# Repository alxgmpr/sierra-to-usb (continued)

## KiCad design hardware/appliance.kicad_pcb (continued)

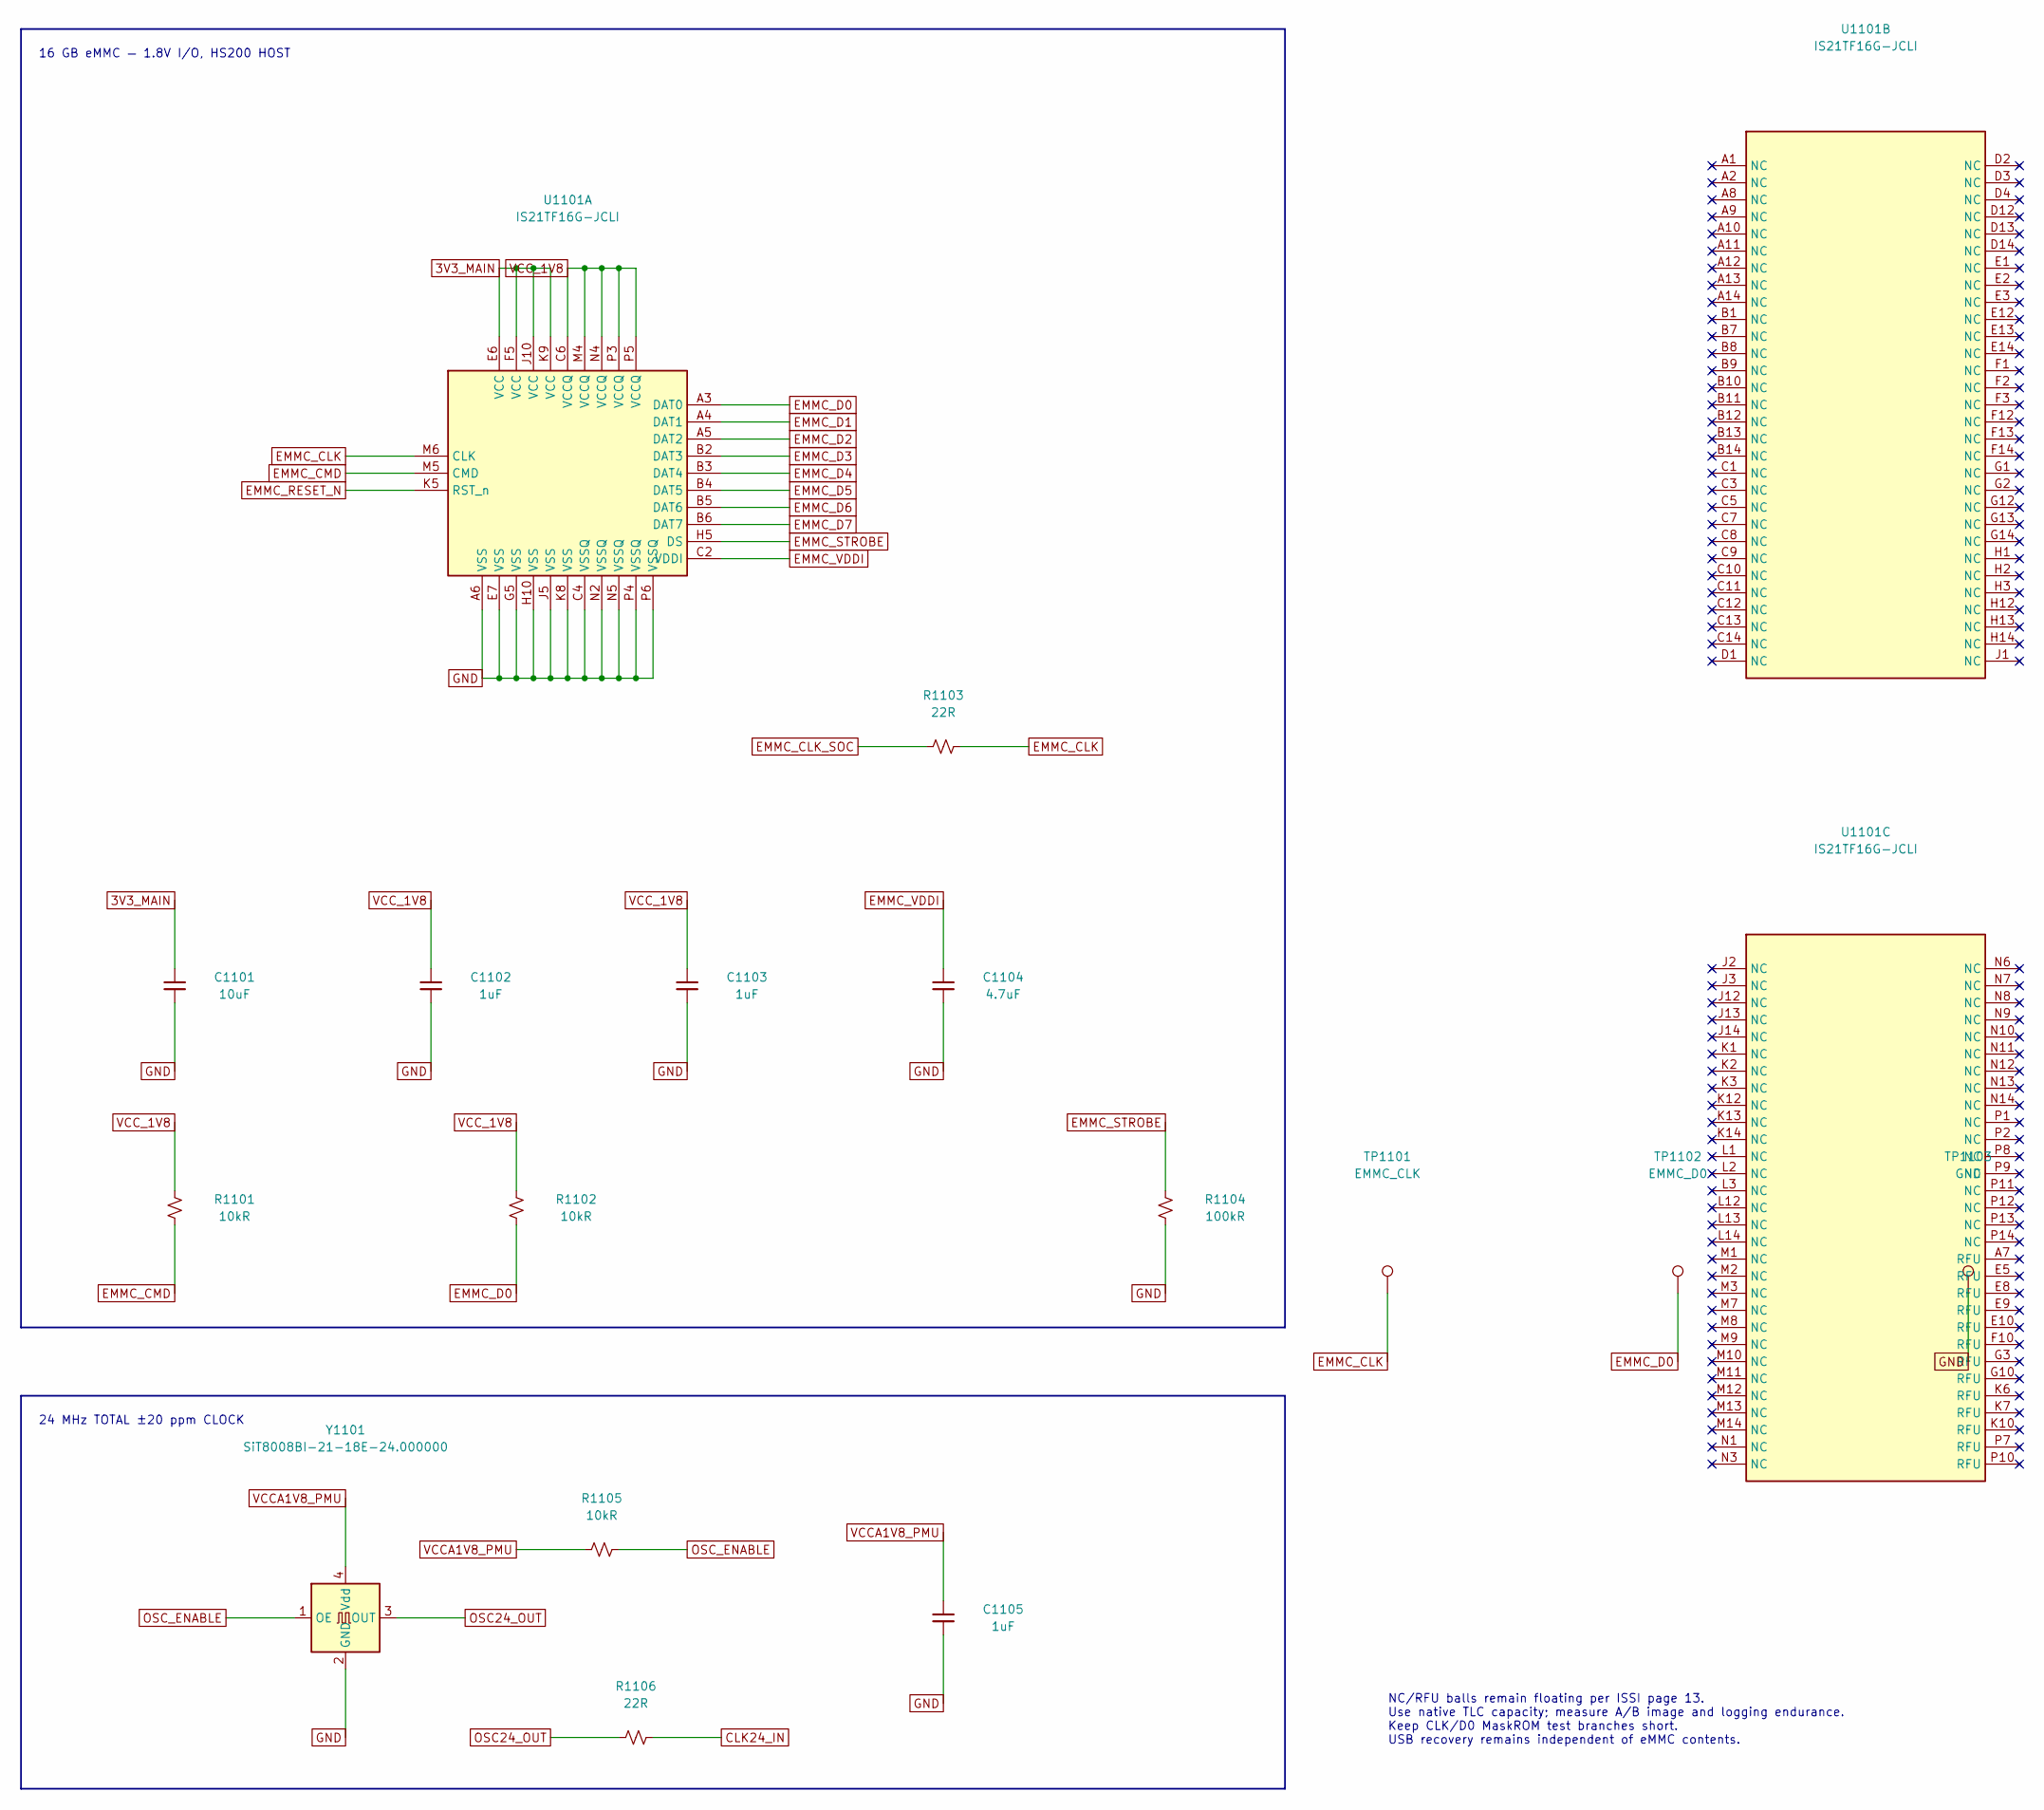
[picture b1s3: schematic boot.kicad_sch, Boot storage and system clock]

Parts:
C1101: 10uF; C_1206_3216Metric_Pad1.33x1.80mm_HandSolder; Tolerance 10%; Voltage Rating 50V; MPN CL31B106KBHNNNE; LCSC C89632
C1102, C1103, C1105: 1uF; C_0402_1005Metric; Tolerance 10%; Voltage Rating 6.3V; MPN CL05B105KQ5NNNC; LCSC C307426
C1104: 4.7uF; C_0402_1005Metric; Voltage Rating 10V; MPN CL05A475MP5NRNC
R1101, R1102, R1105: 10kR; R_0603_1608Metric_Pad0.98x0.95mm_HandSolder; Tolerance 1%; Power Rating 0.1W; MPN RC0603FR-0710KL
R1103, R1106: 22R; R_0603_1608Metric_Pad0.98x0.95mm_HandSolder; Tolerance 1%; Power Rating 0.1W; MPN RC0603FR-0722RL
R1104: 100kR; R_0603_1608Metric_Pad0.98x0.95mm_HandSolder; Tolerance 1%; Power Rating 0.1W; MPN RC0603FR-07100KL
TP1101: EMMC_CLK; TestPoint_Pad_D1.0mm
TP1102: EMMC_D0; TestPoint_Pad_D1.0mm
TP1103: GND; TestPoint_Pad_D1.0mm
U1101: IS21TF16G-JCLI; LFBGA-153_11.5x13mm_Layout14x14_P0.5mm; MPN IS21TF16G-JCLI; LCSC C17441928
Y1101: SiT8008BI-21-18E-24.000000; Oscillator_SMD_SiT_PQFN-4Pin_3.2x2.5mm; Supply Voltage 1.8V; MPN SiT8008BI-21-18E-24.000000; LCSC C820729

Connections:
3V3_MAIN: C1101.1, U1101.E6 (VCC), U1101.F5 (VCC), U1101.J10 (VCC), U1101.K9 (VCC); also elsewhere on the board
CLK24_IN: R1106.2; also elsewhere on the board
EMMC_CLK: R1103.2, TP1101.1 (1_1), U1101.M6 (CLK)
EMMC_CLK_SOC: R1103.1; also elsewhere on the board
EMMC_CMD: R1101.2, U1101.M5 (CMD); also elsewhere on the board
EMMC_D0: R1102.2, TP1102.1 (1_1), U1101.A3 (DAT0); also elsewhere on the board
EMMC_D1: U1101.A4 (DAT1); also elsewhere on the board
EMMC_D2: U1101.A5 (DAT2); also elsewhere on the board
EMMC_D3: U1101.B2 (DAT3); also elsewhere on the board
EMMC_D4: U1101.B3 (DAT4); also elsewhere on the board
EMMC_D5: U1101.B4 (DAT5); also elsewhere on the board
EMMC_D6: U1101.B5 (DAT6); also elsewhere on the board
EMMC_D7: U1101.B6 (DAT7); also elsewhere on the board
EMMC_RESET_N: U1101.K5 (RST_n); also elsewhere on the board
EMMC_STROBE: R1104.1, U1101.H5 (DS); also elsewhere on the board
EMMC_VDDI: C1104.1, U1101.C2 (VDDI)
GND: C1101.2, C1102.2, C1103.2, C1104.2, C1105.2, R1104.2, TP1103.1 (1_1), U1101.A6 (VSS), U1101.C4 (VSSQ), U1101.E7 (VSS), U1101.G5 (VSS), U1101.H10 (VSS), U1101.J5 (VSS), U1101.K8 (VSS), U1101.N2 (VSSQ), U1101.N5 (VSSQ), U1101.P4 (VSSQ), U1101.P6 (VSSQ), Y1101.2 (GND); also elsewhere on the board
OSC24_OUT: R1106.1, Y1101.3 (OUT)
OSC_ENABLE: R1105.2, Y1101.1 (OE); also elsewhere on the board
VCCA1V8_PMU: C1105.1, R1105.1, Y1101.4 (Vdd); also elsewhere on the board
VCC_1V8: C1102.1, C1103.1, R1101.1, R1102.1, U1101.C6 (VCCQ), U1101.M4 (VCCQ), U1101.N4 (VCCQ), U1101.P3 (VCCQ), U1101.P5 (VCCQ); also elsewhere on the board

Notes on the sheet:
16 GB eMMC — 1.8V I/O, HS200 HOST
NC/RFU balls remain floating per ISSI page 13. Use native TLC capacity; measure A/B image and logging endurance. Keep CLK/D0 MaskROM test branches short. USB recovery remains independent of eMMC contents.
24 MHz TOTAL ±20 ppm CLOCK

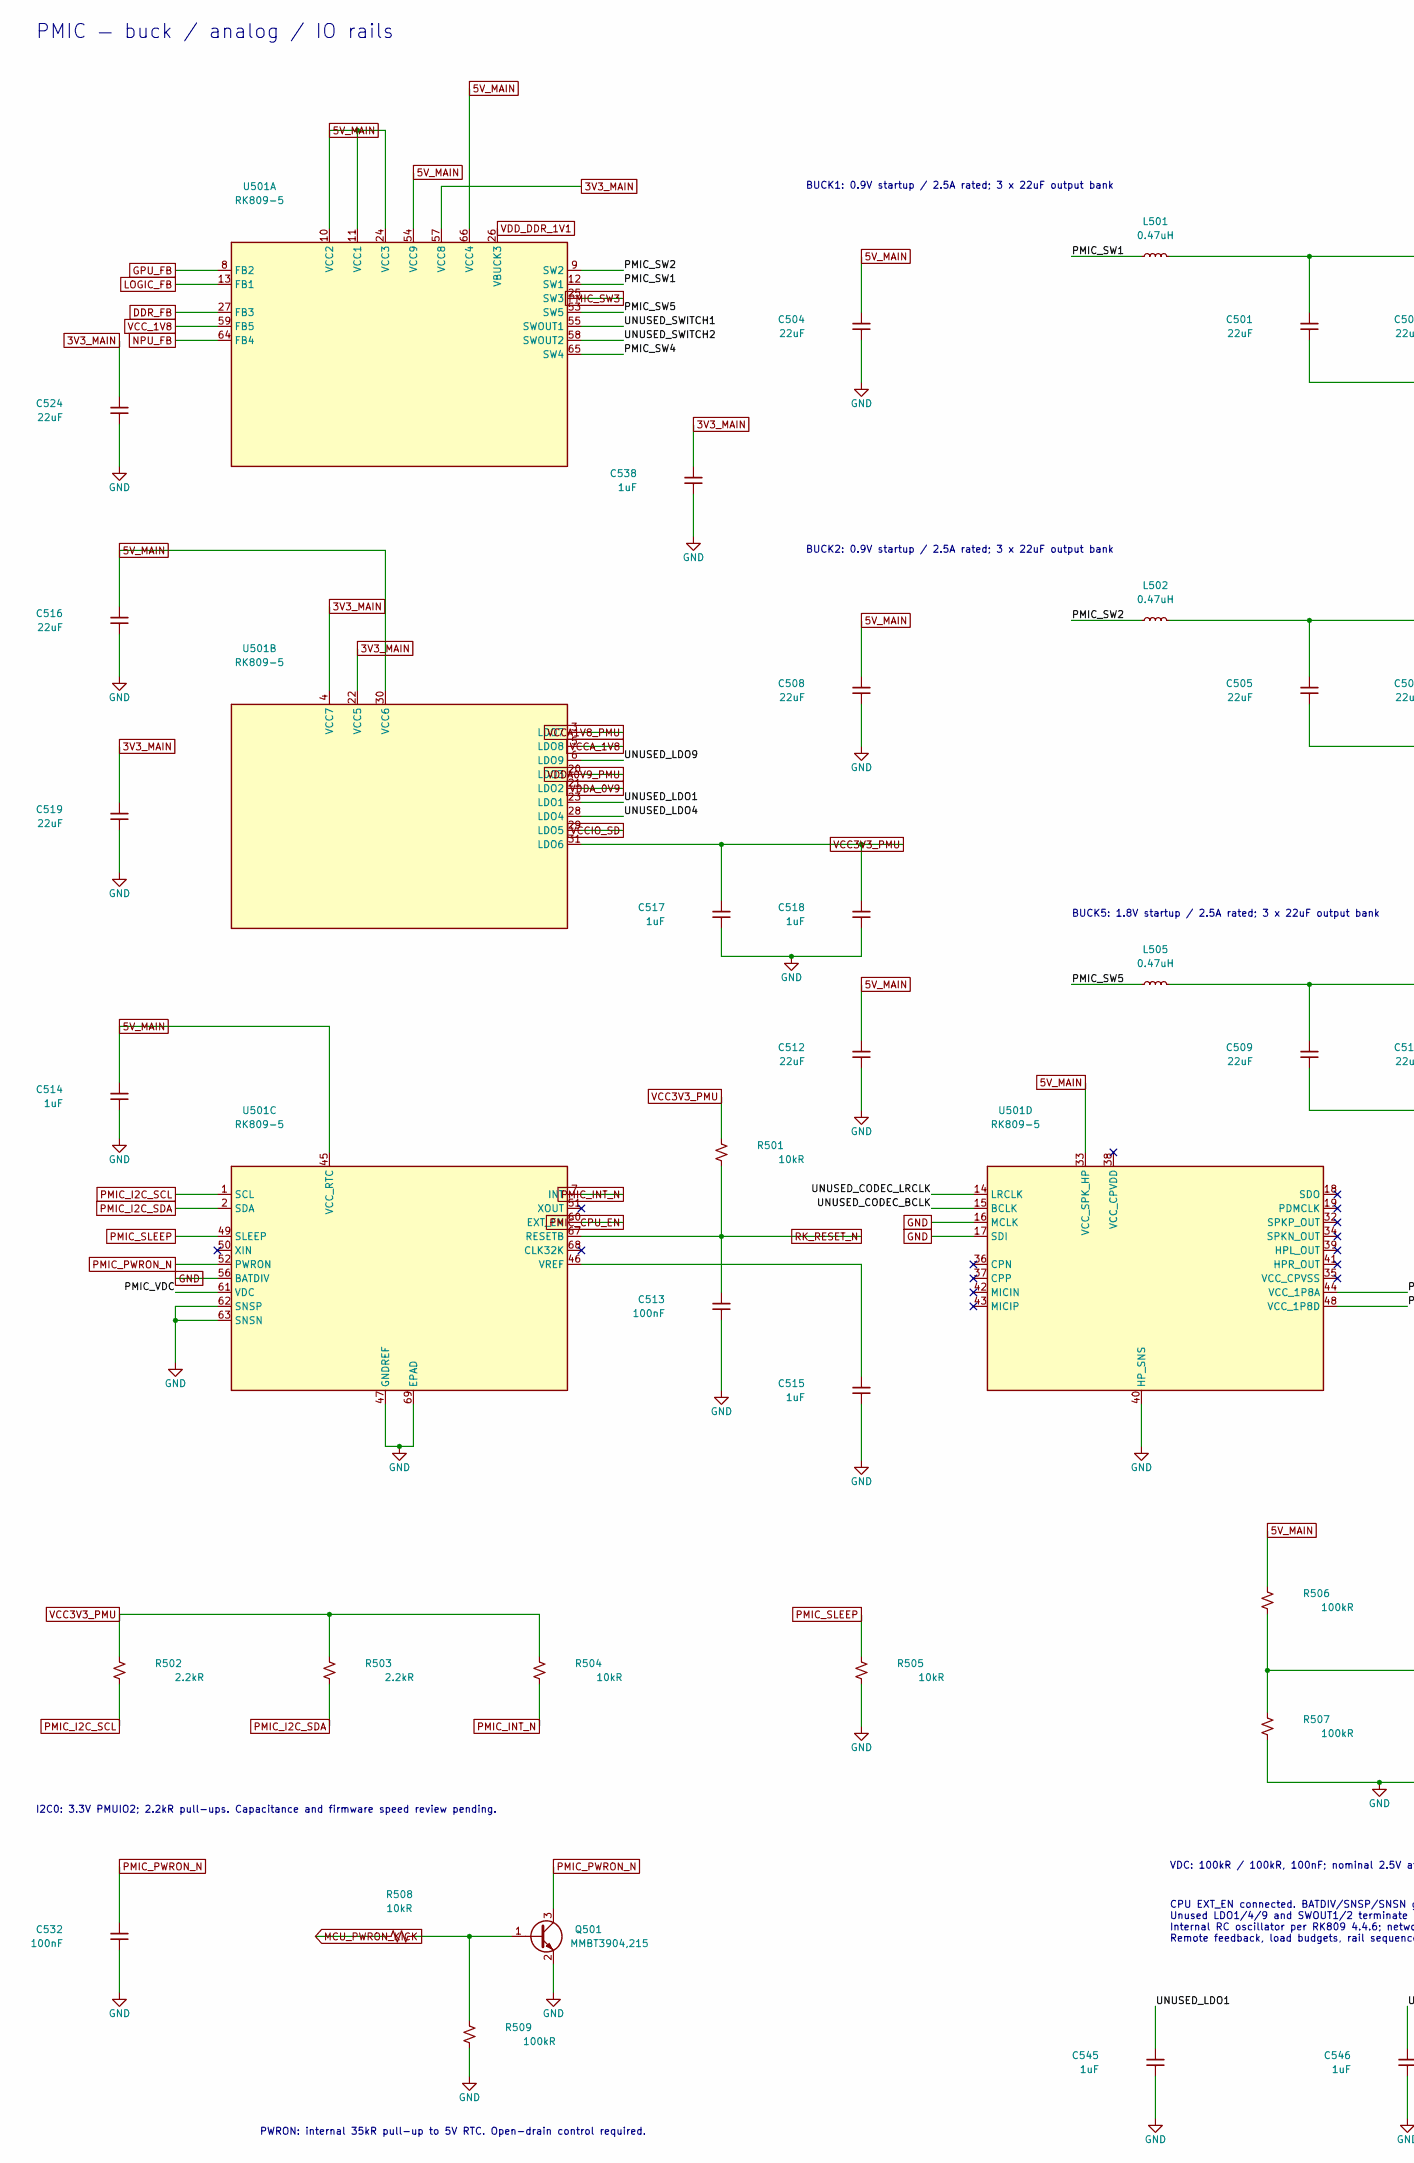
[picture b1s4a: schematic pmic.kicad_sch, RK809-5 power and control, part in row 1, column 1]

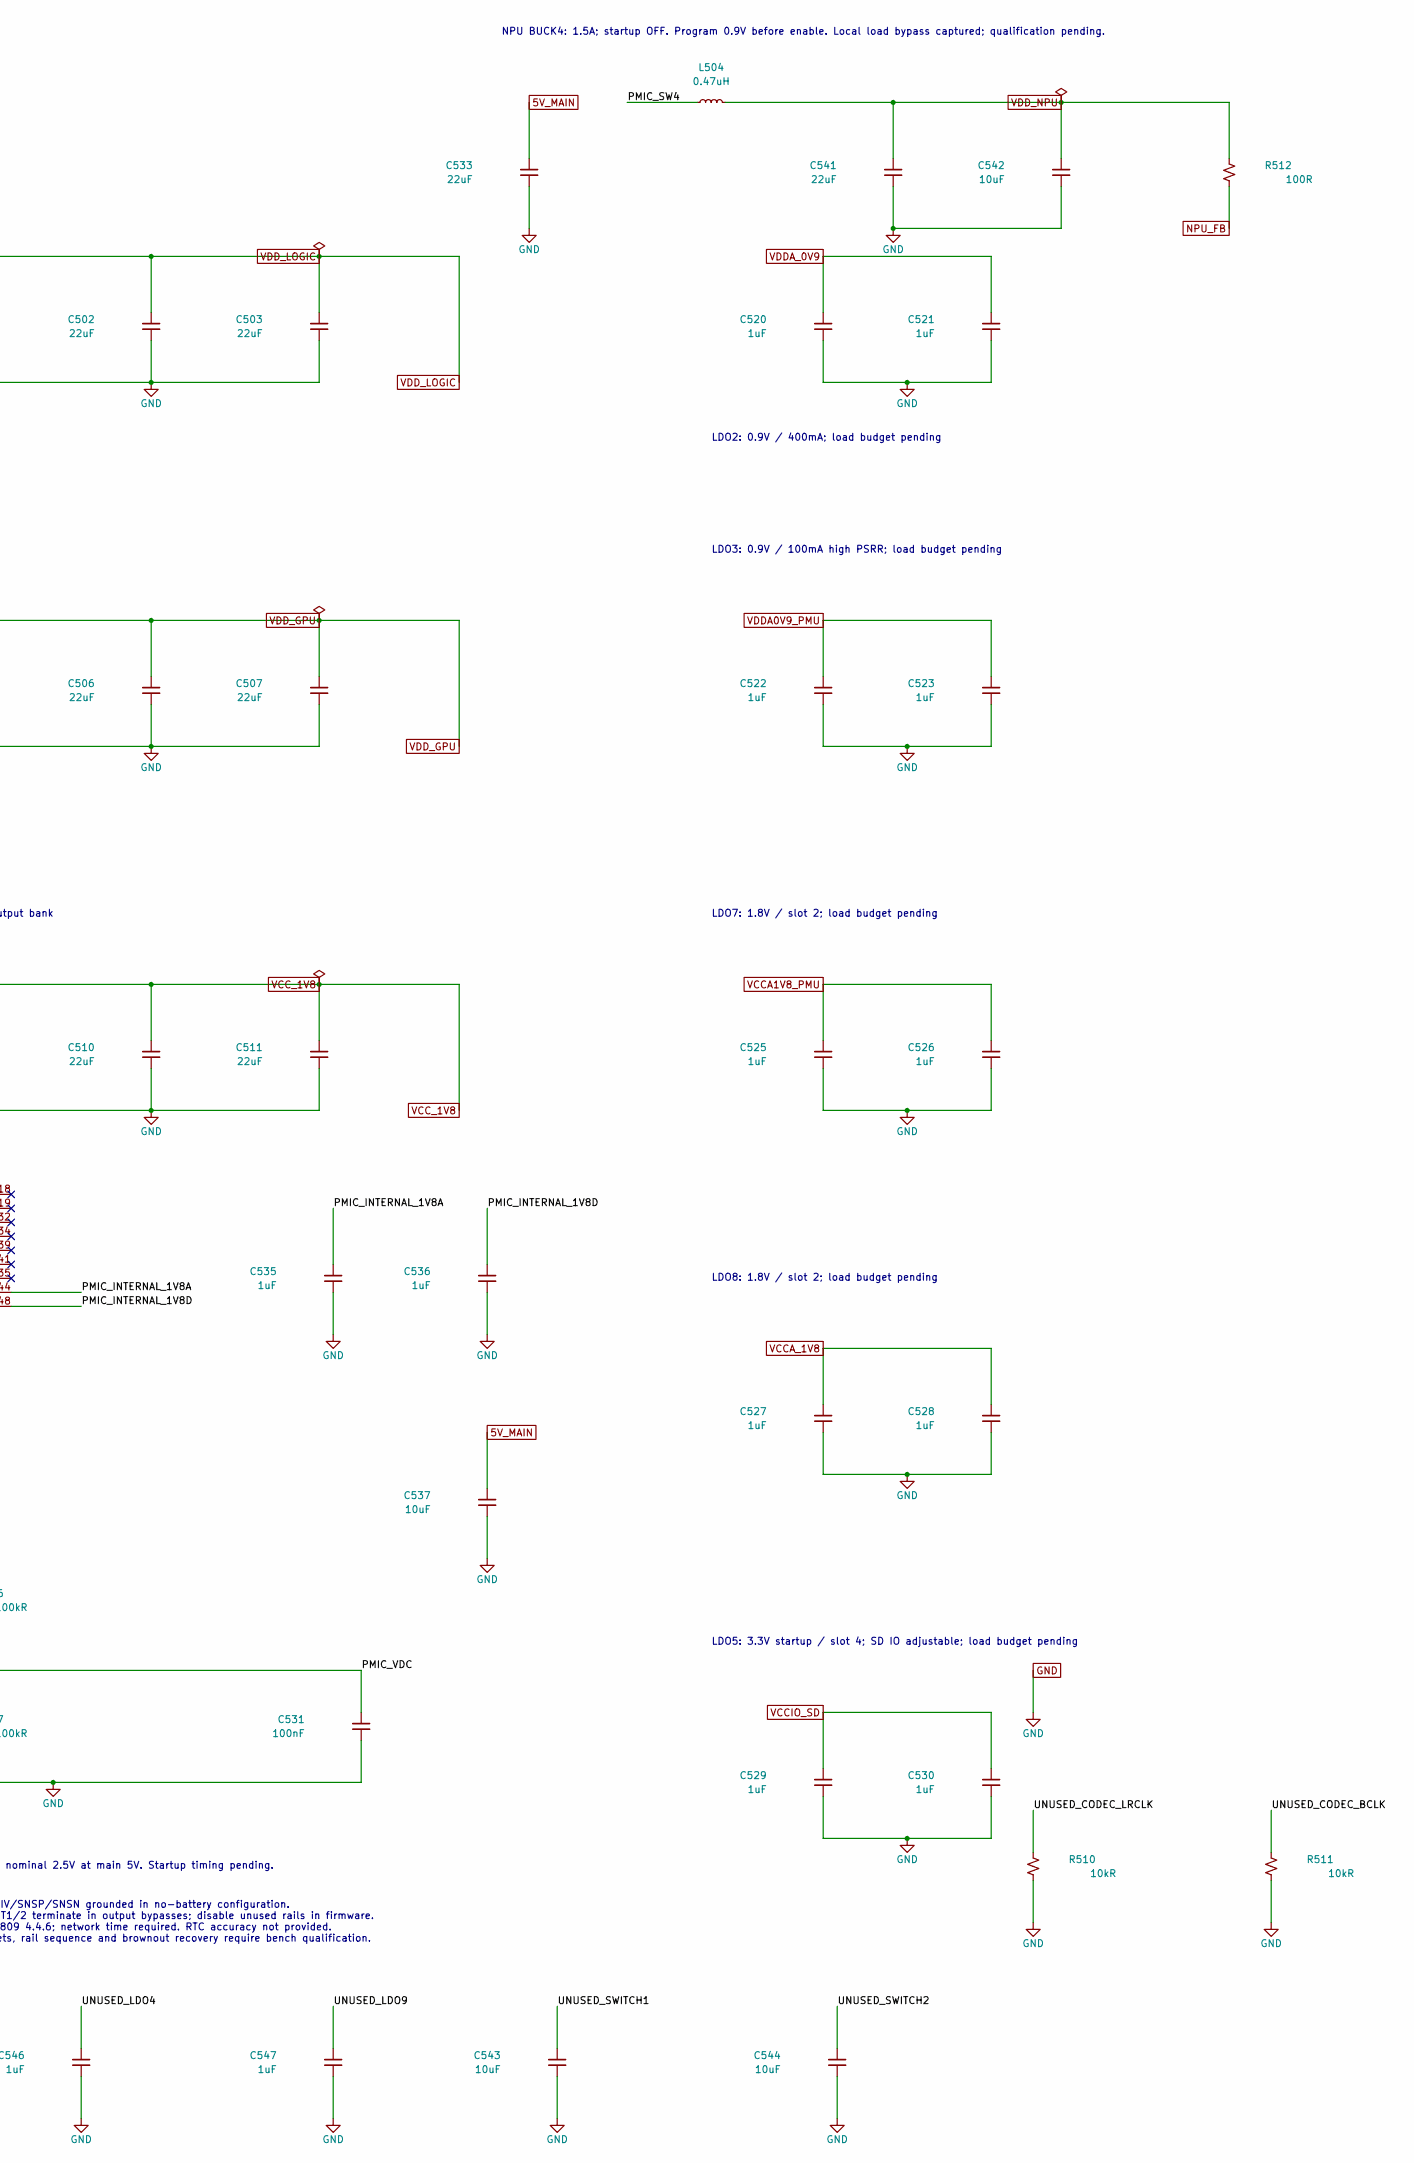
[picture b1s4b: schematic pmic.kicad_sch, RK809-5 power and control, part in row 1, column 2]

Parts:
C501, C502, C503, C504, C505, C506, C507, C508, C509, C510, C511, C512, C516, C519, C524, C533, C541: 22uF; C_1210_3225Metric_Pad1.33x2.70mm_HandSolder; Tolerance 10%; Voltage Rating 25V; MPN CL32B226KAJNNNE; LCSC C309062
C513, C531, C532: 100nF; C_0603_1608Metric_Pad1.08x0.95mm_HandSolder; Tolerance 10%; Voltage Rating 25V; MPN CL10B104KA8NNNC; LCSC C1590
C514, C515, C517, C518, C520, C521, C522, C523, C525, C526, C527, C528, C529, C530, C535, C536, C538, C545, C546, C547: 1uF; C_0603_1608Metric_Pad1.08x0.95mm_HandSolder; Tolerance 10%; Voltage Rating 25V; MPN CL10B105KA8NNNC; LCSC C29936
C537, C542, C543, C544: 10uF; C_1206_3216Metric_Pad1.33x1.80mm_HandSolder; Tolerance 10%; Voltage Rating 50V; MPN CL31B106KBHNNNE; LCSC C89632
L501, L502, L504, L505: 0.47uH; L_Coilcraft_XxL4020; MPN XGL4020-471MEC; LCSC C5837785
Q501: MMBT3904,215; SOT-23_Handsoldering; MPN MMBT3904,215
R501, R504, R505, R508, R510, R511: 10kR; R_0603_1608Metric_Pad0.98x0.95mm_HandSolder; Tolerance 1%; Power Rating 0.1W; MPN RC0603FR-0710KL; LCSC C98220
R502, R503: 2.2kR; R_0603_1608Metric_Pad0.98x0.95mm_HandSolder; Tolerance 1%; Power Rating 0.1W; MPN RC0603FR-072K2L; LCSC C114662
R506, R507, R509: 100kR; R_0603_1608Metric_Pad0.98x0.95mm_HandSolder; Tolerance 1%; Power Rating 0.1W; MPN RC0603FR-07100KL; LCSC C14675
R512: 100R; R_0603_1608Metric_Pad0.98x0.95mm_HandSolder; Tolerance 1%; Power Rating 0.1W; MPN RC0603FR-07100RL; LCSC C105588
U501: RK809-5; ArtInChip_QFN-68-1EP_7x7mm_P0.35mm_EP5.49x5.49mm_ThermalVias; MPN RK809-5; LCSC C2939628

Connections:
3V3_MAIN: C519.1, C524.1, C538.1, U501.4 (VCC7), U501.22 (VCC5), U501.57 (VCC8); also elsewhere on the board
5V_MAIN: C504.1, C508.1, C512.1, C514.1, C516.1, C533.1, C537.1, R506.1, U501.10 (VCC2), U501.11 (VCC1), U501.24 (VCC3), U501.30 (VCC6), U501.33 (VCC_SPK_HP), U501.45 (VCC_RTC), U501.54 (VCC9), U501.66 (VCC4); also elsewhere on the board
/Processor PMIC/PMIC_INTERNAL_1V8A: C535.1, U501.44 (VCC_1P8A)
/Processor PMIC/PMIC_INTERNAL_1V8D: C536.1, U501.48 (VCC_1P8D)
/Processor PMIC/PMIC_SW1: L501.1, U501.12 (SW1)
/Processor PMIC/PMIC_SW2: L502.1, U501.9 (SW2)
/Processor PMIC/PMIC_SW4: L504.1, U501.65 (SW4)
/Processor PMIC/PMIC_SW5: L505.1, U501.53 (SW5)
/Processor PMIC/PMIC_VDC: C531.1, R506.2, R507.1, U501.61 (VDC)
/Processor PMIC/UNUSED_CODEC_BCLK: R511.1, U501.15 (BCLK)
/Processor PMIC/UNUSED_CODEC_LRCLK: R510.1, U501.14 (LRCLK)
/Processor PMIC/UNUSED_LDO1: C545.1, U501.23 (LDO1)
/Processor PMIC/UNUSED_LDO4: C546.1, U501.28 (LDO4)
/Processor PMIC/UNUSED_LDO9: C547.1, U501.6 (LDO9)
/Processor PMIC/UNUSED_SWITCH1: C543.1, U501.55 (SWOUT1)
/Processor PMIC/UNUSED_SWITCH2: C544.1, U501.58 (SWOUT2)
DDR_FB: U501.27 (FB3); also elsewhere on the board
GND: C501.2, C502.2, C503.2, C504.2, C505.2, C506.2, C507.2, C508.2, C509.2, C510.2, C511.2, C512.2, C513.2, C514.2, C515.2, C516.2, C517.2, C518.2, C519.2, C520.2, C521.2, C522.2, C523.2, C524.2, C525.2, C526.2, C527.2, C528.2, C529.2, C530.2, C531.2, C532.2, C533.2, C535.2, C536.2, C537.2, C538.2, C541.2, C542.2, C543.2, C544.2, C545.2, C546.2, C547.2, Q501.2 (E), R505.2, R507.2, R509.2, R510.2, R511.2, U501.16 (MCLK), U501.17 (SDI), U501.40 (HP_SNS), U501.47 (GNDREF), U501.56 (BATDIV), U501.62 (SNSP), U501.63 (SNSN), U501.69 (EPAD); also elsewhere on the board
GPU_FB: U501.8 (FB2); also elsewhere on the board
LOGIC_FB: U501.13 (FB1); also elsewhere on the board
MCU_PWRON_KICK: R508.1; also elsewhere on the board
NPU_FB: R512.2, U501.64 (FB4); also elsewhere on the board
unnamed: Q501.1 (B), R508.2, R509.1
unnamed: C515.1, U501.46 (VREF)
PMIC_CPU_EN: U501.60 (EXT_EN); also elsewhere on the board
PMIC_I2C_SCL: R502.2, U501.1 (SCL); also elsewhere on the board
PMIC_I2C_SDA: R503.2, U501.2 (SDA); also elsewhere on the board
PMIC_INT_N: R504.2, U501.7 (INT); also elsewhere on the board
PMIC_PWRON_N: C532.1, Q501.3 (C), U501.52 (PWRON); also elsewhere on the board
PMIC_SLEEP: R505.1, U501.49 (SLEEP); also elsewhere on the board
PMIC_SW3: U501.25 (SW3); also elsewhere on the board
RK_RESET_N: C513.1, R501.2, U501.67 (RESETB); also elsewhere on the board
VCC3V3_PMU: C517.1, C518.1, R501.1, R502.1, R503.1, R504.1, U501.31 (LDO6); also elsewhere on the board
VCCA1V8_PMU: C525.1, C526.1, U501.3 (LDO7); also elsewhere on the board
VCCA_1V8: C527.1, C528.1, U501.5 (LDO8); also elsewhere on the board
VCCIO_SD: C529.1, C530.1, U501.29 (LDO5); also elsewhere on the board
VCC_1V8: C509.1, C510.1, C511.1, L505.2, U501.59 (FB5); also elsewhere on the board
VDDA0V9_PMU: C522.1, C523.1, U501.20 (LDO3); also elsewhere on the board
VDDA_0V9: C520.1, C521.1, U501.21 (LDO2); also elsewhere on the board
VDD_DDR_1V1: U501.26 (VBUCK3); also elsewhere on the board
VDD_GPU: C505.1, C506.1, C507.1, L502.2; also elsewhere on the board
VDD_LOGIC: C501.1, C502.1, C503.1, L501.2; also elsewhere on the board
VDD_NPU: C541.1, C542.1, L504.2, R512.1; also elsewhere on the board

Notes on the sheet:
LDO7: 1.8V / slot 2; load budget pending
LDO2: 0.9V / 400mA; load budget pending
LDO3: 0.9V / 100mA high PSRR; load budget pending
VDC: 100kR / 100kR, 100nF; nominal 2.5V at main 5V. Startup timing pending.
PWRON: internal 35kR pull-up to 5V RTC. Open-drain control required.
BUCK2: 0.9V startup / 2.5A rated; 3 x 22uF output bank
CPU EXT_EN connected. BATDIV/SNSP/SNSN grounded in no-battery configuration. Unused LDO1/4/9 and SWOUT1/2 terminate in output bypasses; disable unused rails in firmware. Internal RC oscillator per RK809 4.4.6; network time required. RTC accuracy not provided. Remote feedback, load budgets, rail seq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
LDO8: 1.8V / slot 2; load budget pending
LDO5: 3.3V startup / slot 4; SD IO adjustable; load budget pending
I2C0: 3.3V PMUIO2; 2.2kR pull-ups. Capacitance and firmware speed review pending.
PMIC — buck / analog / IO rails
NPU BUCK4: 1.5A; startup OFF. Program 0.9V before enable. Local load bypass captured; qualification pending.
BUCK1: 0.9V startup / 2.5A rated; 3 x 22uF output bank
BUCK5: 1.8V startup / 2.5A rated; 3 x 22uF output bank

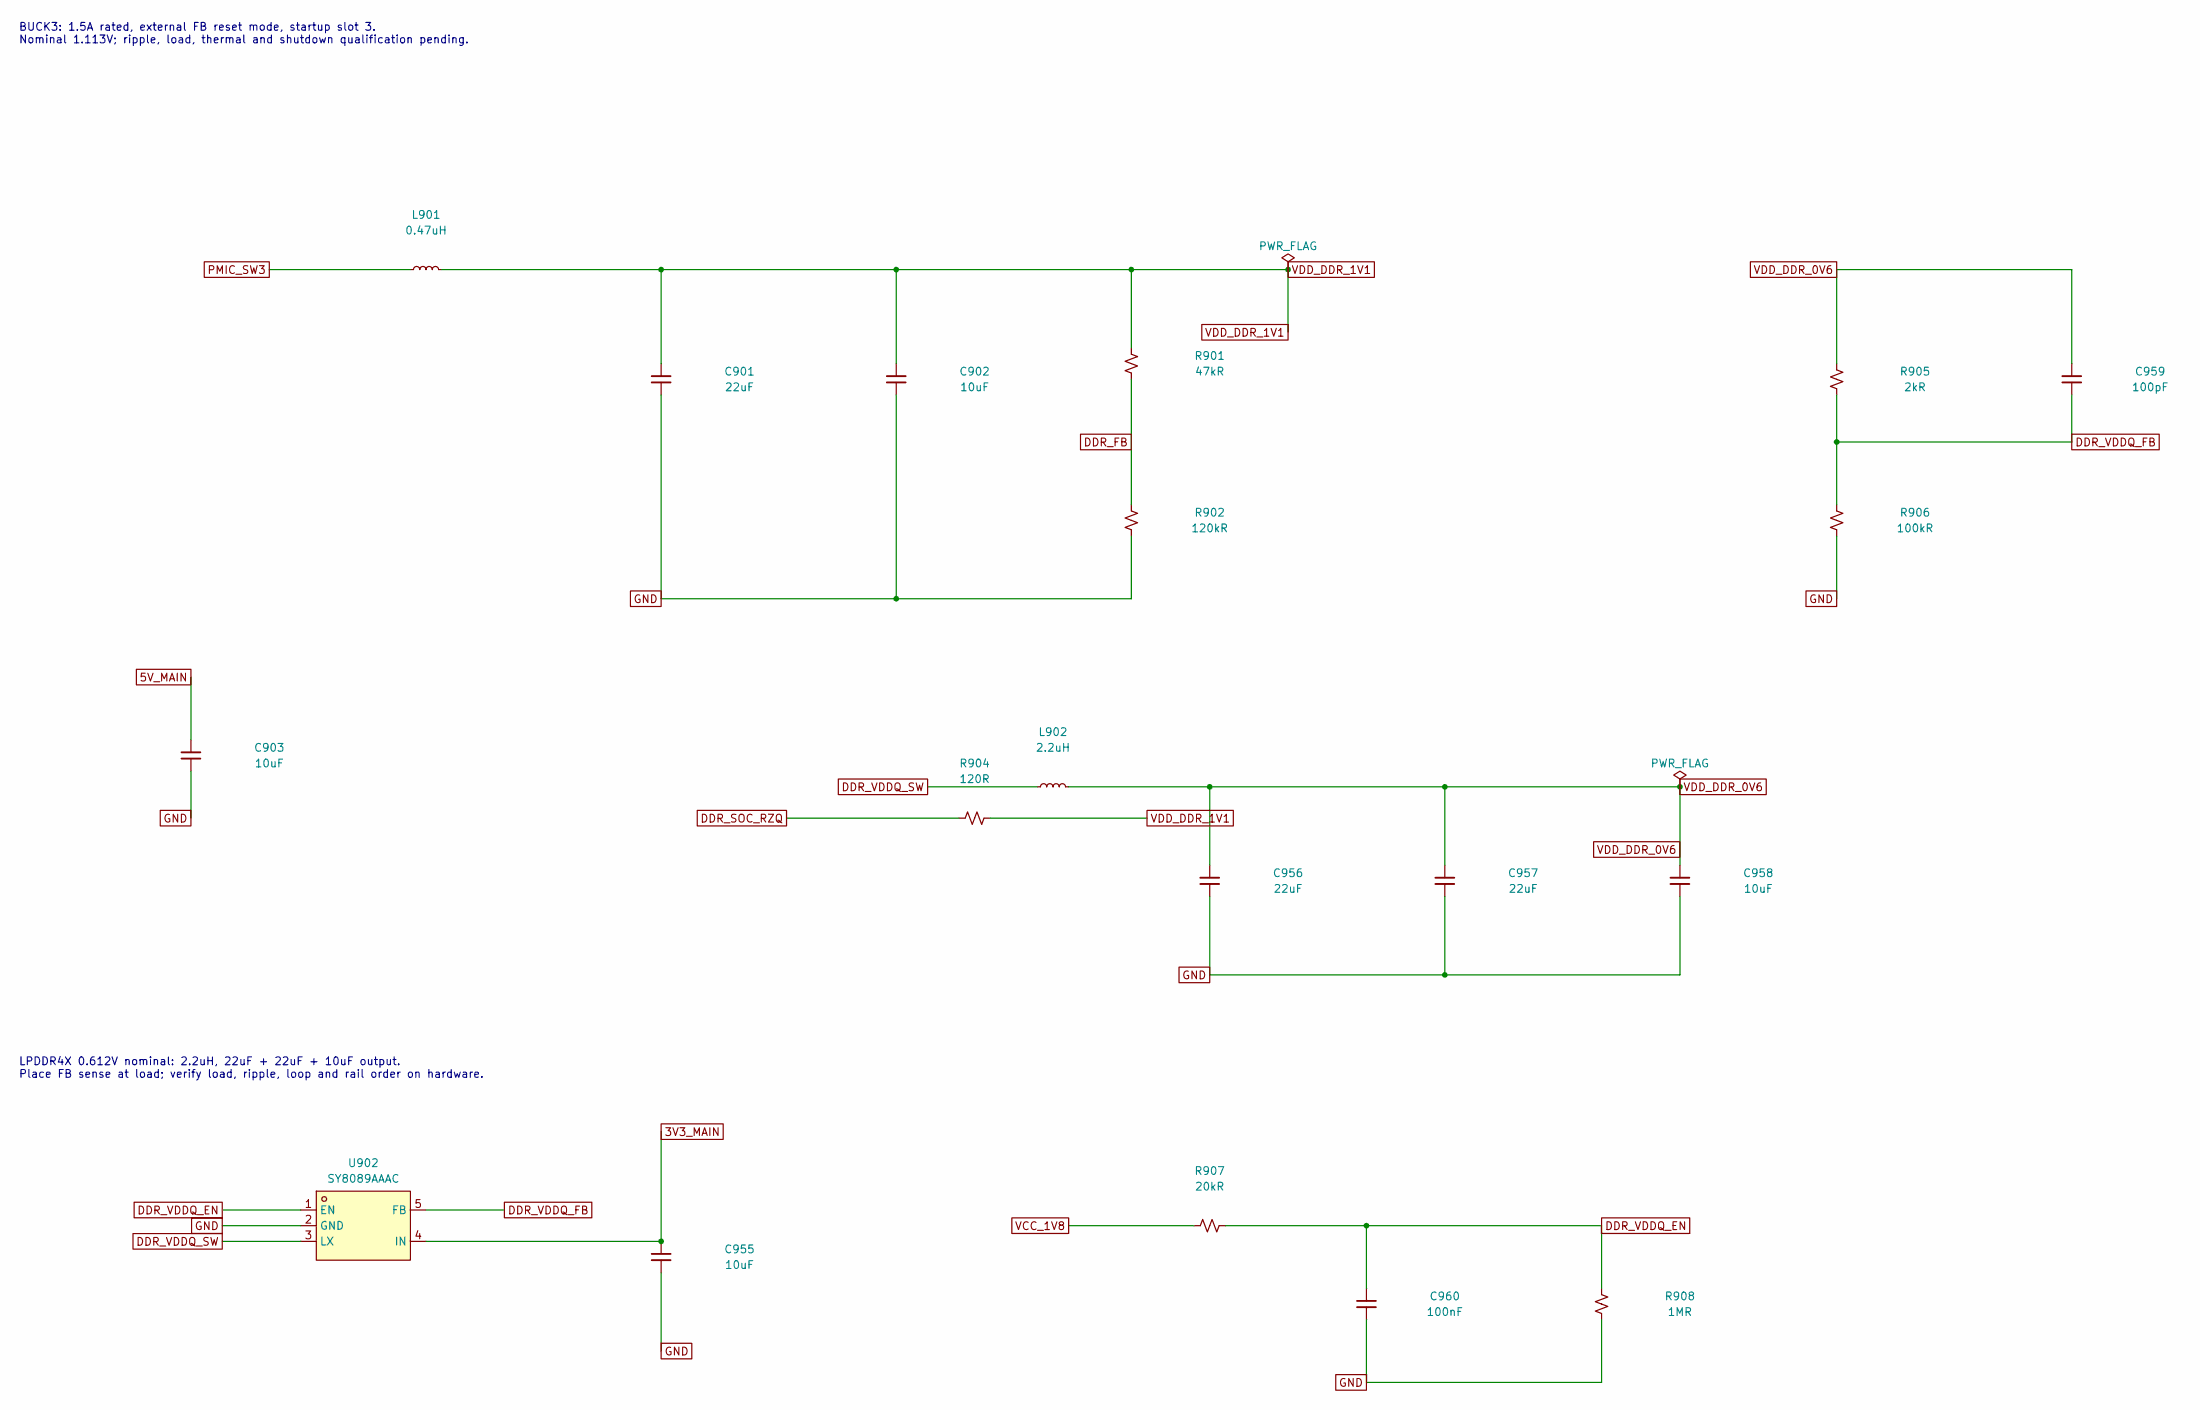
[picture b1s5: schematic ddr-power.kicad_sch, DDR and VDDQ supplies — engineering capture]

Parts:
C901, C956, C957: 22uF; C_1210_3225Metric_Pad1.33x2.70mm_HandSolder; Tolerance 10%; Voltage Rating 25V; MPN CL32B226KAJNNNE; LCSC C309062
C902, C903, C955, C958: 10uF; C_1206_3216Metric_Pad1.33x1.80mm_HandSolder; Tolerance 10%; Voltage Rating 50V; MPN CL31B106KBHNNNE; LCSC C89632
C959: 100pF; C_0603_1608Metric_Pad1.08x0.95mm_HandSolder; Voltage Rating 50V; Tolerance 5%; MPN CL10C101JB8NNNC; LCSC C14858
C960: 100nF; C_0603_1608Metric_Pad1.08x0.95mm_HandSolder; Voltage Rating 25V; Tolerance 10%; MPN CL10B104KA8NNNC; LCSC C1590
L901: 0.47uH; L_Coilcraft_XxL4020; MPN XGL4020-471MEC; LCSC C5837785
L902: 2.2uH; L_Coilcraft_XxL4020; Inductance Tolerance 20%; MPN XGL4020-222MEC
R901: 47kR; R_0603_1608Metric_Pad0.98x0.95mm_HandSolder; Tolerance 1%; Power Rating 0.1W; MPN RC0603FR-0747KL; LCSC C105579
R902: 120kR; R_0603_1608Metric_Pad0.98x0.95mm_HandSolder; Tolerance 1%; Power Rating 0.1W; MPN RC0603FR-07120KL; LCSC C114607
R904: 120R; R_0603_1608Metric_Pad0.98x0.95mm_HandSolder; Tolerance 1%; Power Rating 0.1W; MPN RC0603FR-07120RL; LCSC C114640
R905: 2kR; R_0603_1608Metric_Pad0.98x0.95mm_HandSolder; Tolerance 1%; Power Rating 0.1W; MPN RC0603FR-072KL; LCSC C105576
R906: 100kR; R_0603_1608Metric_Pad0.98x0.95mm_HandSolder; Tolerance 1%; Power Rating 0.1W; MPN RC0603FR-07100KL; LCSC C14675
R907: 20kR; R_0603_1608Metric_Pad0.98x0.95mm_HandSolder; Tolerance 1%; Power Rating 0.1W; MPN RC0603FR-0720KL; LCSC C105575
R908: 1MR; R_0603_1608Metric_Pad0.98x0.95mm_HandSolder; Tolerance 1%; Power Rating 0.1W; MPN RC0603FR-071ML; LCSC C105578
U902: SY8089AAAC; SOT-23-5_HandSoldering; MPN SY8089AAAC; LCSC C78988

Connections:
3V3_MAIN: C955.1, U902.4 (IN); also elsewhere on the board
5V_MAIN: C903.1; also elsewhere on the board
DDR_FB: R901.2, R902.1; also elsewhere on the board
DDR_SOC_RZQ: R904.1; also elsewhere on the board
DDR_VDDQ_EN: C960.1, R907.2, R908.1, U902.1 (EN); also elsewhere on the board
DDR_VDDQ_FB: C959.2, R905.2, R906.1, U902.5 (FB)
DDR_VDDQ_SW: L902.1, U902.3 (LX)
GND: C901.2, C902.2, C903.2, C955.2, C956.2, C957.2, C958.2, C960.2, R902.2, R906.2, R908.2, U902.2 (GND); also elsewhere on the board
PMIC_SW3: L901.1; also elsewhere on the board
VCC_1V8: R907.1; also elsewhere on the board
VDD_DDR_0V6: C956.1, C957.1, C958.1, C959.1, L902.2, R905.1; also elsewhere on the board
VDD_DDR_1V1: C901.1, C902.1, L901.2, R901.1, R904.2; also elsewhere on the board

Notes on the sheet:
BUCK3: 1.5A rated, external FB reset mode, startup slot 3. Nominal 1.113V; ripple, load, thermal and shutdown qualification pending.
LPDDR4X 0.612V nominal: 2.2uH, 22uF + 22uF + 10uF output. Place FB sense at load; verify load, ripple, loop and rail order on hardware.
